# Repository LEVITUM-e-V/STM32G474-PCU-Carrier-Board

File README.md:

# PCB PCU

Carrier board for the Levitum PCU (Power Control Unit), revision B, 2026-11. The board takes a WeAct STM32G474 module and brings out the PCU's measurement and communication interfaces: voltage, current and temperature sensing, CAN, RS-232, I²C and digital I/O.

It is a 4-layer board, 101 × 77 mm, designed in KiCad 7.0.5.

**Status:** routed and checked. DRC shows 0 errors and 0 unconnected nets, and the schematic matches the board. The board has not been manufactured yet, so it is untested in hardware.

## What is on the board

| Function | Details |
|---|---|
| MCU | WeAct STM32G474CoreBoard Long (STM32G474CEU6), plugged into two 1×24 sockets (J4, J5) |
| Supply | 5 V in on J1, TVS protection, 3.3 V LDO (AP2112K-3.3) for the on-board logic |
| Voltage sensing | 2 × 50 V (J3) and 2 × 5 V (J12) differential inputs |
| Current sensing | 4 × Hall sensor inputs, SIG/REF, bidirectional around 1.65 V (J8) |
| Temperature sensing | 2 × PT1000 inputs (J9) |
| Communication | 2 × CAN for a redundant DroneCAN bus: CAN1 on FDCAN2 (J2), CAN2 on FDCAN3 (J11); RS-232 (MAX3221) and I²C (J13) |
| Digital I/O | 4 outputs, 2 inputs (J10) |
| Debug | 40 test pads on the bottom side, including a debug UART (TP44 TX, TP45 RX, TP46 GND) |

### Connectors

All board connectors are Molex Micro-Fit 3.0, right angle. Each function has its own size where possible, so cables cannot be swapped by accident.

| Ref | Size | Molex part | Function |
|---|---|---|---|
| J1 | 2×2 | 43045-0400 | 5 V supply in |
| J2 | 2×2 | 43045-0400 | CAN1 (same pinout as J11) |
| J13 | 2×3 | 43045-0600 | RS-232 and I²C |
| J3 | 2×2 | 43045-0400 | Voltage sensing, 2 × 50 V. **Same size as J1, J11 and J12: colour-code this cable** |
| J12 | 2×2 | 43045-0400 | Voltage sensing, 2 × 5 V |
| J8 | 2×5 | 43045-1000 | Hall current sensors |
| J9 | 2×4 | 43045-0800 | 2 PT1000 temperature sensors (pins 5 and 6 unused) |
| J10 | 2×4 | 43045-0800 | Digital inputs and outputs |
| J11 | 2×2 | 43045-0400 | CAN2 (second, redundant CAN bus) |

J9 and J10 share the same 8-pin size. Label those two cables. J13 is the only 6-pin connector.

J1, J2, J3, J11 and J12 share the same 4-pin size. **The 50 V plug (J3) fits J1, J2, J11 and J12.** In J1 it puts 50 V on the 5 V rail and destroys the board and the module; in J2 or J11 it destroys the CAN transceiver. The 5 V supply plug (J1) in J2 or J11 shorts the 5 V supply to GND. The two CAN cables (J2, J11) have the same pinout and may be swapped. Give the J3 cable its own colour and the others different colours (owner decision, 2026-11-13).

**50 V sense wires:** fit a series resistor of at least 10 kΩ (or a fuse of at most 100 mA) in each 50 V positive wire, close to where it taps the 50 V source. It limits every wrong plug-in of the J3 cable to a few milliamps, and an unprotected sense wire from the stack is a hazard even when it is plugged in correctly. A 10 kΩ resistor changes the channel gain by about 5 %, which the calibration removes.

## Repository layout

| Folder | Contents |
|---|---|
| `kicad/` | The KiCad project: `PCB PCU.kicad_pro`, schematic (root sheet plus 8 sub-sheets), routed board, project symbol library `PCU.kicad_sym`, footprint library `PCU_Molex.pretty` |
| `production/` | Ready-to-upload manufacturing files: Gerbers and drill files (also zipped) and the placement file |
| `bom/` | Parts list as CSV (JLCPCB column layout) and as a readable Markdown table |
| `scripts/` | Read-only check scripts and the script that regenerates `production/` |

## Ordering the board

What you need to open, check and order the board is listed in [REQUIREMENTS.md](REQUIREMENTS.md). In short:

1. Upload `production/PCB_PCU-gerbers.zip` to the PCB manufacturer. Choose 4 layers and 1.6 mm thickness.
2. For assembly, upload `bom/BOM_PCU_G474.csv` and `production/PCB_PCU-pos.csv`. The "LCSC Part #" column in the BOM is still empty: fill it in, or let the assembler match the parts by manufacturer part number.
3. Check the assembler's placement preview, especially the rotation of ICs and diodes, before confirming.

### Parts that are not assembled by the manufacturer

| Parts | What happens |
|---|---|
| R105, R106 | Left empty on purpose. They are the 5 V I²C pull-ups. The 3.3 V pull-ups R107 and R108 are fitted instead. Fit **either** pair, never both. |
| J4, J5 | Soldered by hand after delivery: Würth 61302411821 (1×24 socket, 2.54 mm). |

These four parts are excluded from the placement file and from the assembled lines of the BOM.

Bought separately: the WeAct STM32G474 module, the Micro-Fit mating housings (43025 series) with crimp terminals (43030 series), and the sensors.

## Changing the design

1. Open `kicad/PCB PCU.kicad_pro` in KiCad 7.0.5.
2. Make the change in the schematic, then update the board from the schematic.
3. Run DRC, then the checks in `scripts/` (see [scripts/README.md](scripts/README.md)).
4. Run `sh scripts/make_production.sh` to regenerate the manufacturing files.

Keep the project file name `PCB PCU`. The reference designators in the schematic are stored under that project name.

## Documentation

The design documentation (schematic PDFs, design notes, routing plan with the change log, layout checklist and review reports) is kept internally at Levitum and is not part of this repository. To view the schematic, open `kicad/PCB PCU.kicad_pro` in KiCad 7.0.5.

## Open points

- The board has not been built or tested yet.
- The firmware still targets the previous MCU (STM32U575) and has to be ported to the STM32G474. It is not part of this repository.
- Unanswered system questions: whether the PCU is an end of the CAN buses (CAN1 and CAN2 termination is fitted by default), what the digital outputs drive, and which Hall sensor type is used.

## Credits and use

This board was designed at Levitum and is Levitum's property. You are welcome to use it as a starting point for your own PCU or STM32G474 carrier board. If it helps you, a shout-out to Levitum is appreciated.

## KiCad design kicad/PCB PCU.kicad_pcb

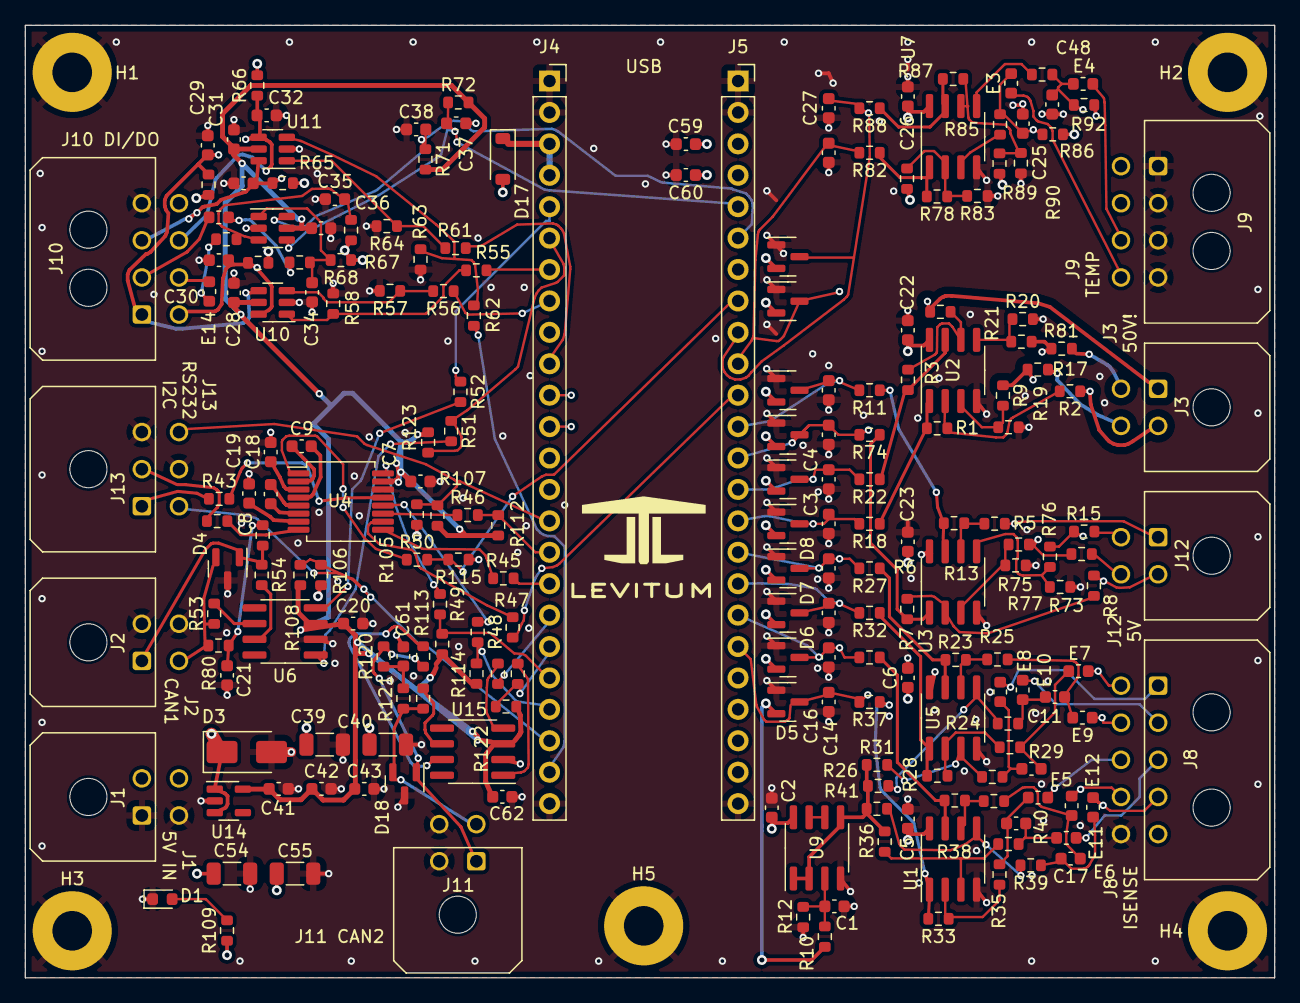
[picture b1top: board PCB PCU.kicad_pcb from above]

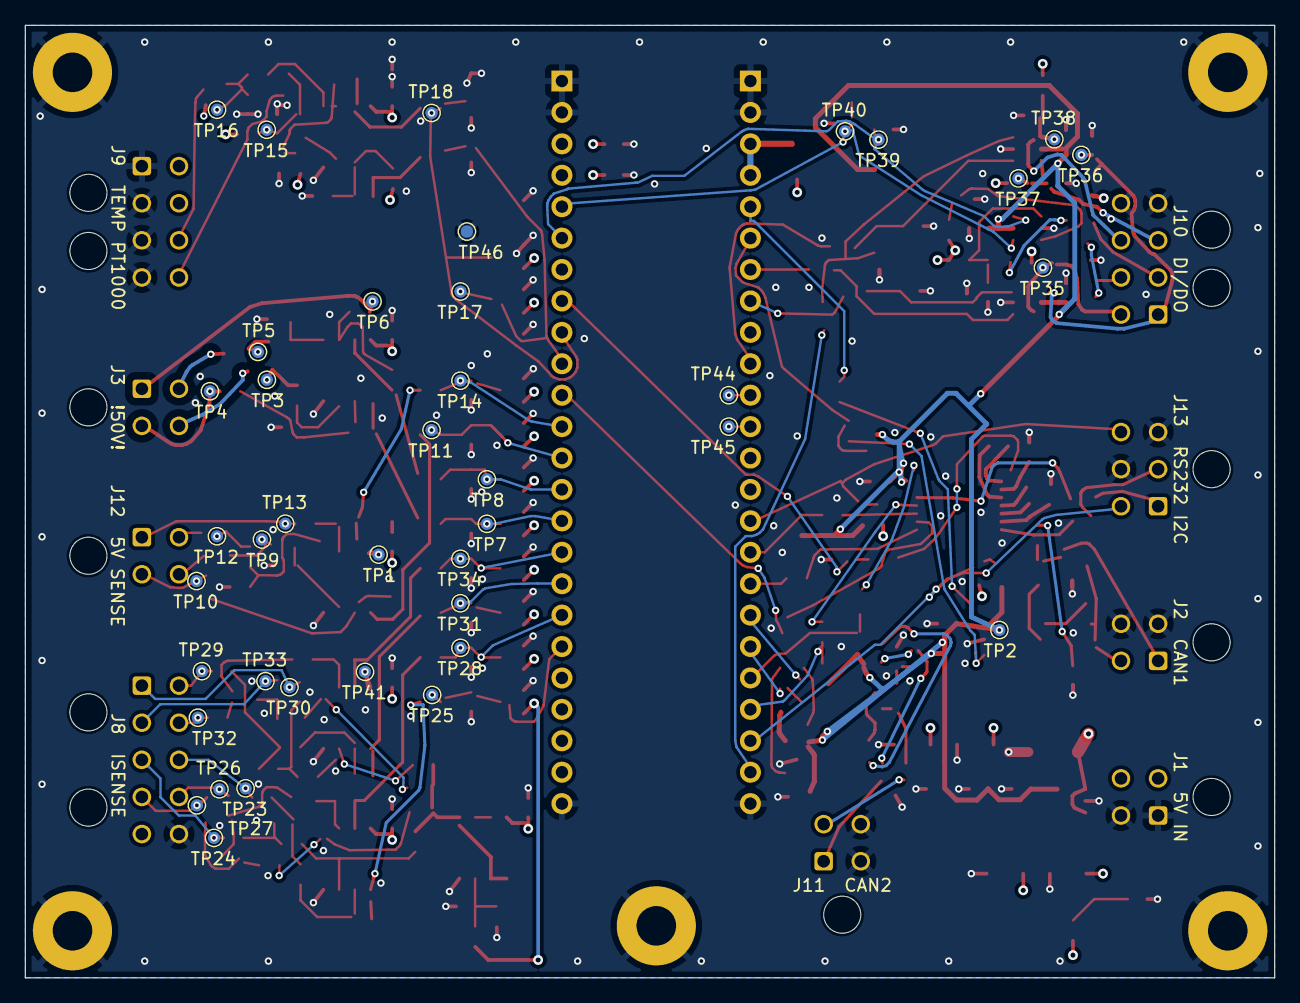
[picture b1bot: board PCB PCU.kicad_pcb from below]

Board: 4 copper layers, 101.0 x 77.0 mm, 255 parts (40 on the bottom side), 145 nets.

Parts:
C1, C2, C5, C6, C22, C23, C26, C42, C43: 0.1uF; C_0603_1608Metric
C3, C4, C7, C8, C9, C10, C11, C12, C13, C14, C15, C16, C17, C18, C19, C20, C21, C24, C25, C27, C28, C29, C30, C31, C32, C33, C34, C35, C36, C37, C38, C45, C47, C48, C61, C62: 0.1 uF; C_0603_1608Metric
C39, C40, C54, C55: 10uF; C_1206_3216Metric
C41: 10uF; C_0603_1608Metric
C59: 1uF; C_0603_1608Metric
C60: 100nF; C_0603_1608Metric
D1: 150060VS55040; LED_0603_1608Metric
D3: SMAJ5.0A; D_SMA
D4, D18: PESD1CAN,215; SOT-23
D5, D6, D7, D8, D9, D10, D11, D12, D13, D14: BAT54S; SOT-23
D17: B5819W; D_SOD-123
E3, E4, E5, E6, E7, E8, E9, E10, E11, E12, E13, E14: HZ0603B102R-10; L_0603_1608Metric
H1, H2, H3, H4, H5: MountingHole_Pad_M3; MountingHole_3.2mm_M3_Pad
J1, J2, J3, J11, J12: 430450400; Molex_Micro-Fit_3.0_43045-0400_2x02_P3.00mm_Horizontal
J4: WeAct_Long_Type_STM32G474CEU6_LEFT; PinSocket_1x24_P2.54mm_Vertical
J5: WeAct_Long_Type_STM32G474CEU6_RIGHT; PinSocket_1x24_P2.54mm_Vertical
J8: 430451000; Molex_Micro-Fit_3.0_43045-1000_2x05_P3.00mm_Horizontal
J9, J10: 430450800; Molex_Micro-Fit_3.0_43045-0800_2x04_P3.00mm_Horizontal
J13: 430450600; Molex_Micro-Fit_3.0_43045-0600_2x03_P3.00mm_Horizontal
R1, R3, R19, R20: 11k 0.1%; R_0603_1608Metric
R2, R4: 200k 0.1%; R_0603_1608Metric
R5, R8: 20k 0.1%; R_0603_1608Metric
R6, R7, R10, R12, R13, R15, R73, R75, R76, R77: 10k 0.1%; R_0603_1608Metric
R9, R17, R21, R81: 100k 0.1%; R_0603_1608Metric
R11, R18, R22, R27, R32, R37, R42, R74, R82, R88, R105, R106, R107, R108: 4.7k; R_0603_1608Metric
R23, R26, R28, R31, R33, R36, R38, R41: 16k 0.1%; R_0603_1608Metric
R24, R25, R29, R30, R34, R35, R39, R40: 10k 1%; R_0603_1608Metric
R43, R44, R45, R46, R47, R48, R49, R50, R51, R52, R53, R54, R116, R117, R118, R119: 0; R_0603_1608Metric
R55, R56, R61, R62, R71, R72, R122: 1k; R_0603_1608Metric
R57, R58, R63, R64, R112, R113, R114, R115: 100k; R_0603_1608Metric
R59, R60, R65, R66, R67, R68, R123: 10k; R_0603_1608Metric
R69, R70: 220; R_0603_1608Metric
R78, R87: 8.2k 0.1%; R_0603_1608Metric
R79, R80, R120, R121: 60.4; R_0603_1608Metric
R83, R89: 2.4k 0.1%; R_0603_1608Metric
R84, R90: 2.7k 0.1%; R_0603_1608Metric
R85, R91: 100; R_0603_1608Metric
R86, R92: 1.5k 0.1%; R_0603_1608Metric
R109: 560; R_0603_1608Metric
TP1, TP2, TP3, TP4, TP5, TP6, TP7, TP8, TP9, TP10, TP11, TP12, TP13, TP14, TP15, TP16, TP17, TP18, TP23, TP24, TP25, TP26, TP27, TP28, TP29, TP30, TP31, TP32, TP33, TP34, TP35, TP36, TP37, TP38, TP39, TP40, TP41: TestPoint; TestPoint_Pad_D1.0mm
TP44: PA9_DBG_TX; TestPoint_Pad_D1.0mm
TP45: PA10_DBG_RX; TestPoint_Pad_D1.0mm
TP46: DBG_GND; TestPoint_Pad_D1.0mm
U1, U2, U3, U5, U7, U9: TLV2186IDR; SOIC-8_3.9x4.9mm_P1.27mm
U4: MAX3221IDBR; SSOP-16_5.3x6.2mm_P0.65mm
U6, U15: TCAN332GDR; SOIC-8_3.9x4.9mm_P1.27mm
U10, U11, U12: SN74LVC2G07DBVR; SOT-23-6
U14: AP2112K-3.3; SOT-23-5

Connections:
5V_1_NEG: J12.2, R8.1, TP10.1
5V_1_POS: J12.4, R73.1
5V_2_NEG: J12.1, R5.1, TP13.1
5V_2_POS: J12.3, R15.1
50V_1_NEG: J3.2, R2.1, TP4.1
50V_1_POS: J3.4, R17.1
50V_2_NEG: J3.1, R4.1, TP6.1
50V_2_POS: J3.3, R81.1
+3.3V: C7.1, C20.1, C28.1, C31.1, C36.1, C41.1, C42.1, C43.1, C62.1, R71.2, R72.2, R107.1, R108.1, R112.1, R113.1, R114.1, R122.2, R123.2, TP2.1, U4.15 (VCC), U6.3 (VCC), U10.5 (VCC), U11.5 (VCC), U12.5 (VCC), U14.5 (VOUT), U15.3 (VCC)
+3V3_MCU: C59.1, C60.1, D5.2 (K), D6.2 (K), D7.2 (K), D8.2 (K), D9.2 (K), D10.2 (K), D11.2 (K), D12.2 (K), D13.2 (K), D14.2 (K), J5.3 (3V3), J5.4 (3V3), R10.1
+5V: C2.1, C5.1, C6.1, C22.1, C23.1, C26.1, C39.1, C40.1, C54.1, C55.1, D3.1 (K), D17.2 (A), J1.2, J1.4, J8.5, R59.2, R60.2, R65.2, R66.2, R67.1, R68.1, R84.1, R86.2, R90.1, R92.2, R105.1, R106.1, R109.1, TP1.1, TP41.1, U1.8 (V+), U2.8 (V+), U3.8 (V+), U5.8 (V+), U7.8 (V+), U9.8 (V+), U14.1 (VIN), U14.3 (EN)
CAN2_H: D18.1 (A1), J11.1, R119.1, R120.2
CAN2_L: D18.2 (A2), J11.3, R118.1, R121.1
CAN_H: D4.1 (A1), J2.1, R54.1, R79.2
CAN_L: D4.2 (A2), J2.3, R53.1, R80.1
DI1: E13.1, J10.2
DI2: E14.1, J10.6
DO1: C30.1, J10.5, R59.1, TP35.1, U10.6
DO2: C29.1, J10.1, R60.1, TP36.1, U10.4
DO3: C33.1, J10.3, R65.1, TP37.1, U11.6
DO4: C32.1, J10.7, R66.1, TP38.1, U11.4
GND: C1.2, C2.2, C3.2, C4.2, C5.2, C6.2, C7.2, C10.2, C12.2, C14.2, C16.2, C18.2, C19.2, C20.2, C21.2, C22.2, C23.2, C24.2, C25.2, C26.2, C27.2, C28.2, C29.2, C30.2, C31.2, C32.2, C33.2, C34.1, C35.1, C36.2, C37.1, C38.1, C39.2, C40.2, C41.2, C42.2, C43.2, C45.2, C47.2, C48.2, C54.2, C55.2, C59.2, C60.2, C61.2, C62.2, D1.1 (K), D3.2 (A), D4.3 (common), D5.1 (A), D6.1 (A), D7.1 (A), D8.1 (A), D9.1 (A), D10.1 (A), D11.1 (A), D12.1 (A), D13.1 (A), D14.1 (A), D18.3 (common), H1.1, H2.1, H3.1, H4.1, H5.1, J1.1, J1.3, J2.2, J2.4, J4.1 (G), J4.2 (G), J4.24 (G), J5.1 (G), J5.2 (G), J5.24 (G), J8.10, J9.1, J9.2, J9.3, J9.4, J10.4, J10.8, J11.2, J11.4, J13.3, J13.5, R12.2, R19.2, R20.2, R57.2, R58.2, R63.2, R64.2, R75.2, R77.2, R83.1, R89.1, R115.1, TP46.1, U1.4 (V-), U2.4 (V-), U3.4 (V-), U4.14 (GND), U5.4 (V-), U6.2 (GND), U7.4 (V-), U9.4 (V-), U10.2 (GND), U11.2 (GND), U12.2 (GND), U14.2 (GND), U15.2 (GND)
I2C_SCL: J4.15 (A15), J13.6, R105.2, R107.2
I2C_SDA: J4.22 (B7), J13.4, R106.2, R108.2
ISENSE_1_REF: E5.1, J8.8, TP23.1
ISENSE_1_SIG: E6.1, J8.3, TP24.1
ISENSE_2_REF: E11.1, J8.9, TP26.1
ISENSE_2_SIG: E12.1, J8.4, TP27.1
ISENSE_3_REF: E7.1, J8.6, TP29.1
ISENSE_3_SIG: E8.1, J8.1, TP30.1
ISENSE_4_REF: E9.1, J8.7, TP32.1
ISENSE_4_SIG: E10.1, J8.2, TP33.1
MCU_5V_1: C45.1, D11.3 (COM), J5.13 (A6), R74.2, TP11.1
MCU_5V_2: C47.1, D12.3 (COM), J5.12 (A7), R11.2, TP14.1
MCU_50V_1: C3.1, D9.3 (COM), J5.15 (A4), R18.2, TP7.1
MCU_50V_2: C4.1, D10.3 (COM), J5.14 (A5), R22.2, TP8.1
MCU_CAN2_RXD: J4.18 (B3), R117.1
MCU_CAN2_TXD: J4.19 (B4), R116.1, R122.1
MCU_CAN_RXD: J4.5 (B12), R52.1
MCU_CAN_TXD: J4.6 (B13), R51.1, R123.1
MCU_DI1: C38.2, J5.6 (B10), R71.1, TP39.1, U12.6
MCU_DI2: C37.2, J5.5 (B11), R72.1, TP40.1, U12.4
MCU_DO1: J4.7 (B14), R55.1
MCU_DO2: J4.8 (B15), R56.1
MCU_DO3: J4.10 (A8), R61.1
MCU_DO4: J4.23 (B9), R62.1
MCU_ISENSE_1: C14.1, D5.3 (COM), J5.19 (A0), R37.2, TP25.1
MCU_ISENSE_2: C16.1, D6.3 (COM), J5.18 (A1), R42.2, TP28.1
MCU_ISENSE_3: C12.1, D7.3 (COM), J5.17 (A2), R32.2, TP31.1
MCU_ISENSE_4: C10.1, D8.3 (COM), J5.16 (A3), R27.2, TP34.1
MCU_RS232_DIN: J4.16 (C10), R46.2, R112.2
MCU_RS232_EN: J5.8 (B2), R50.2, R115.2
MCU_RS232_FORCEOFF: J4.20 (B5), R49.2, R113.2
MCU_RS232_FORCEON: J4.21 (B6), R48.2, R114.2
MCU_RS232_INVALID: J5.11 (C4), R47.2
MCU_RS232_ROUT: J4.17 (C11), R45.2
MCU_T1: C24.1, D13.3 (COM), J5.10 (B0), R82.2, TP17.1
MCU_T2: C27.1, D14.3 (COM), J5.9 (B1), R88.2, TP18.1
unnamed: C11.1, E9.2, R25.1
unnamed: C11.2, E10.2, R24.1
unnamed: C13.1, E7.2, R30.1
unnamed: C13.2, E8.2, R29.1
unnamed: C15.1, E5.2, R35.1
unnamed: C15.2, E6.2, R34.1
unnamed: C17.1, E11.2, R40.1
unnamed: C17.2, E12.2, R39.1
unnamed: C21.1, R79.1, R80.2
unnamed: C25.1, E3.2, R85.1, R86.1, TP15.1
unnamed: C34.2, R68.2, R70.2, U12.1
unnamed: C35.2, R67.2, R69.2, U12.3
unnamed: C48.1, E4.2, R91.1, R92.1, TP16.1
unnamed: C61.1, R120.1, R121.2
unnamed: D1.2 (A), R109.2
unnamed: D17.1 (K), J4.3 (5V), J4.4 (5V)
unnamed: E13.2, R70.1
unnamed: E14.2, R69.1
unnamed: J4.11 (A9), TP44.1
unnamed: J4.12 (A10), TP45.1
unnamed: R1.2, R18.1, U2.1
unnamed: R7.2, R74.1, U3.1
unnamed: R6.2, R11.1, U3.7
unnamed: R13.1, R73.2, TP9.1
unnamed: R15.2, R76.1, TP12.1
unnamed: R9.1, R17.2, TP3.1
unnamed: R21.1, R81.2, TP5.1
unnamed: R3.2, R22.1, U2.7
unnamed: R23.2, R27.1, U5.7
unnamed: R28.2, R32.1, U5.1
unnamed: R33.2, R37.1, U1.1
unnamed: R38.2, R42.1, U1.7
unnamed: R55.2, R58.1, U10.1
unnamed: R56.2, R57.1, U10.3
unnamed: R61.2, R64.1, U11.1
unnamed: R62.2, R63.1, U11.3
unnamed: R78.2, R82.1, U7.1
unnamed: R87.2, R88.1, U7.7
unnamed: R34.2, R36.2, U1.3 (+)
unnamed: R33.1, R35.2, U1.2 (-)
unnamed: R39.2, R41.2, U1.5 (+)
unnamed: R38.1, R40.2, U1.6 (-)
unnamed: R9.2, R19.1, U2.3 (+)
unnamed: R1.1, R2.2, U2.2 (-)
unnamed: R20.1, R21.2, U2.5 (+)
unnamed: R3.1, R4.2, U2.6 (-)
unnamed: R13.2, R75.1, U3.3 (+)
unnamed: R7.1, R8.2, U3.2 (-)
unnamed: R76.2, R77.1, U3.5 (+)
unnamed: R5.2, R6.1, U3.6 (-)
unnamed: C9.1, U4.2 (C1+)
unnamed: C9.2, U4.4 (C1-)
unnamed: C8.1, U4.5 (C2+)
unnamed: C8.2, U4.6 (C2-)
unnamed: R46.1, U4.11 (DIN)
unnamed: R43.2, U4.13 (DOUT)
unnamed: R48.1, U4.12 (FORCEON)
unnamed: R44.2, U4.8 (RIN)
unnamed: R45.1, U4.9 (ROUT)
unnamed: C18.1, U4.3 (V+)
unnamed: C19.1, U4.7 (V-)
unnamed: R50.1, U4.1 (~EN)
unnamed: R49.1, U4.16 (~FORCEOFF)
unnamed: R47.1, U4.10 (~INVALID)
unnamed: R29.2, R31.2, U5.3 (+)
unnamed: R28.1, R30.2, U5.2 (-)
unnamed: R24.2, R26.2, U5.5 (+)
unnamed: R23.1, R25.2, U5.6 (-)
unnamed: R54.2, U6.7 (CANH)
unnamed: R53.2, U6.6 (CANL)
unnamed: R52.2, U6.4 (RXD)
unnamed: R51.2, U6.1 (TXD)
unnamed: R85.2, U7.3 (+)
unnamed: R78.1, R83.2, R84.2, U7.2 (-)
unnamed: R91.2, U7.5 (+)
unnamed: R87.1, R89.2, R90.2, U7.6 (-)
unnamed: C1.1, R10.2, R12.1, U9.3 (+)
unnamed: U9.6 (-), U9.7
unnamed: R119.2, U15.7 (CANH)
unnamed: R118.2, U15.6 (CANL)
unnamed: R117.2, U15.4 (RXD)
unnamed: R116.2, U15.1 (TXD)
RS232_DOUT: J13.1, R43.1
RS232_RIN: J13.2, R44.1
T_1_SIG: E3.1, J9.8
T_2_SIG: E4.1, J9.7
VREF_1V65: R26.1, R31.1, R36.1, R41.1, U9.1, U9.2 (-), U9.5 (+)

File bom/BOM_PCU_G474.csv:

Comment,Designator,Footprint,Quantity,Description,LCSC Part #,DNP
TLV2186IDR,"U1,U2,U3,U5,U7,U9",SOIC-8_3.9x4.9mm_P1.27mm,6,"Dual op-amp, rail-to-rail, 24 V (TI)",C2057856,
MAX3221IDBR,U4,SSOP-16_5.3x6.2mm_P0.65mm,1,"RS-232 transceiver 3.3 V, 1 ch. (TI)",C105243,
TCAN332GDR,"U6,U15",SOIC-8_3.9x4.9mm_P1.27mm,2,CAN transceiver 3.3 V (TI),C191010,
SN74LVC2G07DBVR,"U10,U11,U12",SOT-23-6,3,"Dual buffer, open-drain (TI)",C37708,
AP2112K-3.3,U14,SOT-23-5,1,LDO 3.3 V 600 mA (Diodes Inc.),C51118,
150060VS55040,D1,LED_0603_1608Metric,1,LED 0603 (Würth),C6390388,
SMAJ5.0A,D3,D_SMA,1,TVS 5 V unidirectional,C83329,
"PESD1CAN,215","D4,D18",SOT-23,2,CAN ESD protection (Nexperia),C15771,
BAT54S,"D5,D6,D7,D8,D9,D10,D11,D12,D13,D14",SOT-23,10,"Dual Schottky (series), ADC clamp",C8592,
B5819W,D17,D_SOD-123,1,Schottky 40 V 1 A,C8598,
430451000,J8,Molex_Micro-Fit_3.0_43045-1000_2x05_P3.00mm_Horizontal,1,"Molex Micro-Fit 3.0, 2×5, right angle",,
430450800,"J9,J10",Molex_Micro-Fit_3.0_43045-0800_2x04_P3.00mm_Horizontal,2,"Molex Micro-Fit 3.0, 2×4, right angle",,
430450400,"J1,J2,J3,J11,J12",Molex_Micro-Fit_3.0_43045-0400_2x02_P3.00mm_Horizontal,5,"Molex Micro-Fit 3.0, 2×2, right angle (J1 5 V in, J2 CAN1, J3 50 V sense, J11 CAN2, J12 5 V sense)",C779799,
430450600,J13,Molex_Micro-Fit_3.0_43045-0600_2x03_P3.00mm_Horizontal,1,"Molex Micro-Fit 3.0, 2×3, right angle (J13 RS-232 + I²C)",C127367,
100nF,"C1,C2,C3,C4,C5,C6,C7,C8,C9,C10,C11,C12,C13,C14,C15,C16,C17,C18,C19,C20,C21,C22,C23,C24,C25,C26,C27,C28,C29,C30,C31,C32,C33,C34,C35,C36,C37,C38,C42,C43,C45,C47,C48,C60,C61,C62",C_0603_1608Metric,46,Capacitor 100nF 0603 X7R,,
10uF,"C39,C40,C54,C55",C_1206_3216Metric,4,Capacitor 10uF 1206 X5R/X7R ≥10 V,,
10uF,C41,C_0603_1608Metric,1,Capacitor 10uF 0603 X5R/X7R ≥10 V,,
1uF,C59,C_0603_1608Metric,1,Capacitor 1uF 0603 X5R/X7R ≥10 V,,
HZ0603B102R-10,"E3,E4,E5,E6,E7,E8,E9,E10,E11,E12,E13,E14",L_0603_1608Metric,12,Ferrite bead 1 kΩ@100 MHz (Laird); LCSC part is the equivalent Sunlord GZ1608D102TF,C35061,
11k 0.1%,"R1,R3,R19,R20",R_0603_1608Metric,4,Resistor 11k Ω 0.1% (precision) 0603,,
200k 0.1%,"R2,R4",R_0603_1608Metric,2,Resistor 200k Ω 0.1% (precision) 0603,,
20k 0.1%,"R5,R8",R_0603_1608Metric,2,Resistor 20k Ω 0.1% (precision) 0603,,
10k 0.1%,"R6,R7,R10,R12,R13,R15,R73,R75,R76,R77",R_0603_1608Metric,10,Resistor 10k Ω 0.1% (precision) 0603,C95204,
100k 0.1%,"R9,R17,R21,R81",R_0603_1608Metric,4,Resistor 100k Ω 0.1% (precision) 0603,,
4.7k,"R11,R18,R22,R27,R32,R37,R42,R74,R82,R88,R107,R108",R_0603_1608Metric,12,Resistor 4.7k Ω 1% 0603,,
16k 0.1%,"R23,R26,R28,R31,R33,R36,R38,R41",R_0603_1608Metric,8,Resistor 16k Ω 0.1% (precision) 0603,,
10k 1%,"R24,R25,R29,R30,R34,R35,R39,R40",R_0603_1608Metric,8,Resistor 10k Ω 1% 0603,,
0,"R43,R44,R45,R46,R47,R48,R49,R50,R51,R52,R53,R54,R116,R117,R118,R119",R_0603_1608Metric,16,Resistor 0 Ω (jumper) 0603,,
1k,"R55,R56,R61,R62,R71,R72,R122",R_0603_1608Metric,7,Resistor 1k Ω 1% 0603,,
100k,"R57,R58,R63,R64,R112,R113,R114,R115",R_0603_1608Metric,8,Resistor 100k Ω 1% 0603,,
10k,"R59,R60,R65,R66,R67,R68,R123",R_0603_1608Metric,7,Resistor 10k Ω 1% 0603,,
220,"R69,R70",R_0603_1608Metric,2,Resistor 220 Ω 1% 0603,,
8.2k 0.1%,"R78,R87",R_0603_1608Metric,2,Resistor 8.2k Ω 0.1% (precision) 0603,,
60.4,"R79,R80,R120,R121",R_0603_1608Metric,4,Resistor 60.4 Ω 1% 0603,,
2.4k 0.1%,"R83,R89",R_0603_1608Metric,2,Resistor 2.4k Ω 0.1% (precision) 0603,,
2.7k 0.1%,"R84,R90",R_0603_1608Metric,2,Resistor 2.7k Ω 0.1% (precision) 0603,,
100,"R85,R91",R_0603_1608Metric,2,Resistor 100 Ω 1% 0603,,
1.5k 0.1%,"R86,R92",R_0603_1608Metric,2,Resistor 1.5k Ω 0.1% (precision) 0603,,
560,R109,R_0603_1608Metric,1,Resistor 560 Ω 1% 0603,,
4.7k,"R105,R106",R_0603_1608Metric,2,Resistor 4.7k Ω 1% 0603,,DNP
